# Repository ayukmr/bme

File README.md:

# bme

Surge concussion detector PCB for BME.

## Schematic

## PCB

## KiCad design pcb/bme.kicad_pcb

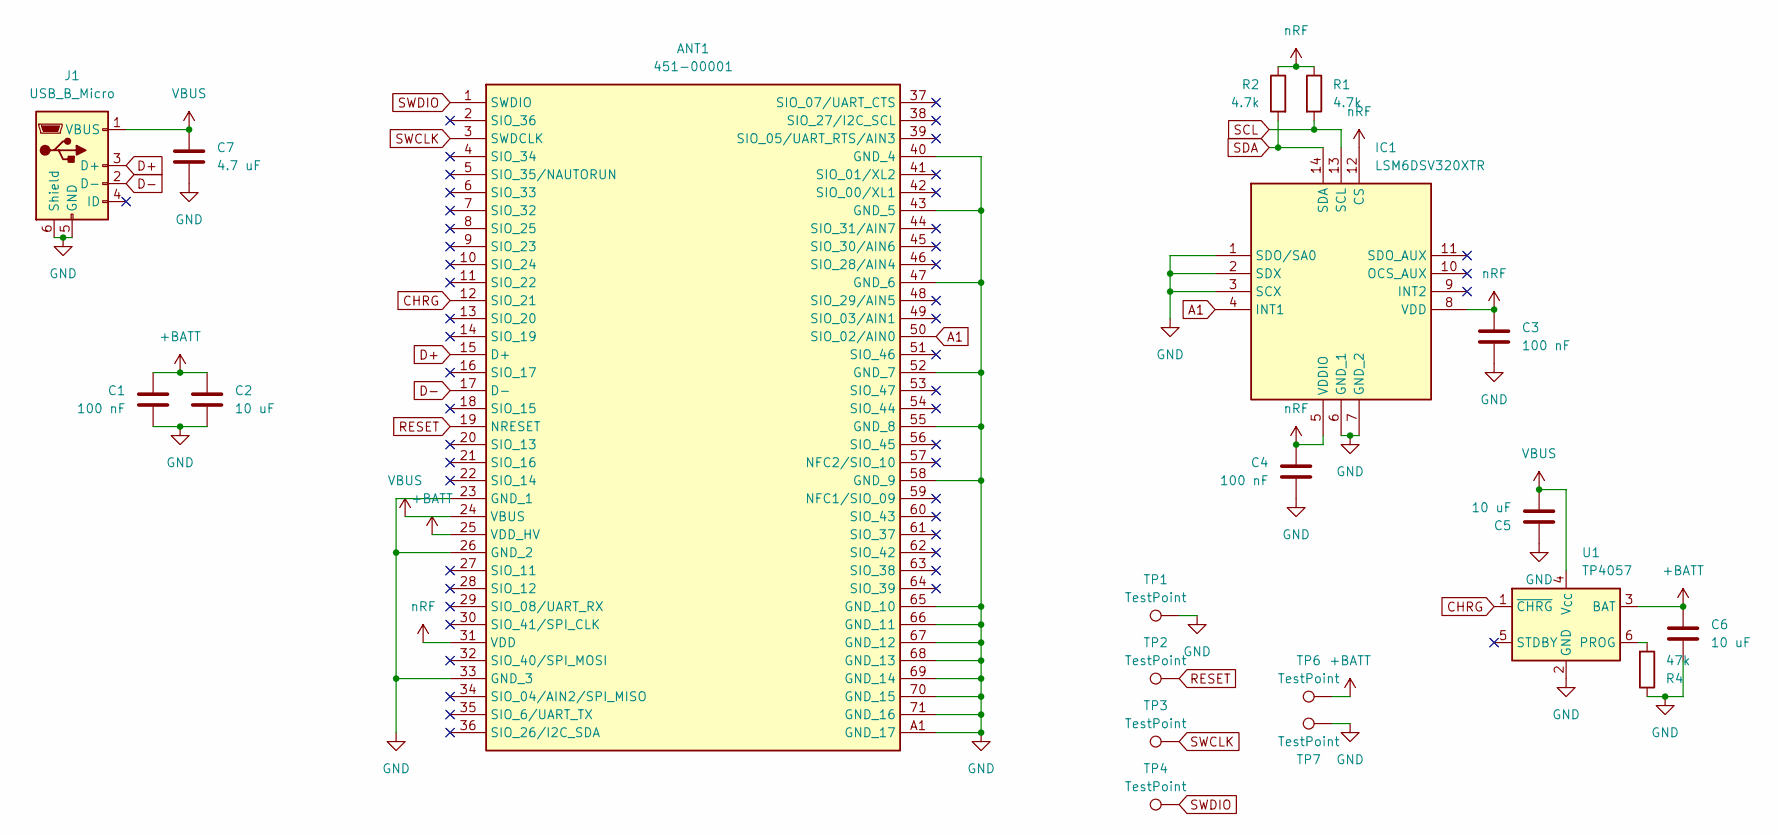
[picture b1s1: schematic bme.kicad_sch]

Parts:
ANT1: 451-00001; 45100001; Manufacturer_Part_Number 451-00001; Mouser Part Number 814-451-00001
C1, C3, C4: 100 nF; C_0603_1608Metric
C2, C5, C6: 10 uF; C_0603_1608Metric
C7: 4.7 uF; C_0603_1608Metric
IC1: LSM6DSV320XTR; LGA-14_3x2.5mm_P0.5mm_LayoutBorder3x4y; Manufacturer_Part_Number LSM6DSV320XTR; Mouser Part Number 511-LSM6DSV320XTR
J1: USB_B_Micro; MICRO-USB-SMD_47346-0001
R1, R2: 4.7k; R_0603_1608Metric
R4: 47k; R_0603_1608Metric
TP1, TP2, TP3, TP4, TP6, TP7: TestPoint; Pad_SMD_1.5x1.5
U1: TP4057; TSOT-23-6

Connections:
+BATT: ANT1.25 (VDD_HV), C1.2, C2.1, C6.2, TP6.1 (1_1), U1.3 (BAT)
A1: ANT1.50 (SIO_02/AIN0), IC1.4 (INT1)
CHRG: ANT1.12 (SIO_21), U1.1 (~CHRG)
D+: ANT1.15 (D+), J1.3 (D+)
D-: ANT1.17 (D-), J1.2 (D-)
GND: ANT1.23 (GND_1), ANT1.26 (GND_2), ANT1.33 (GND_3), ANT1.40 (GND_4), ANT1.43 (GND_5), ANT1.47 (GND_6), ANT1.52 (GND_7), ANT1.55 (GND_8), ANT1.58 (GND_9), ANT1.65 (GND_10), ANT1.66 (GND_11), ANT1.67 (GND_12), ANT1.68 (GND_13), ANT1.69 (GND_14), ANT1.70 (GND_15), ANT1.71 (GND_16), ANT1.A1 (GND_17), C1.1, C2.2, C3.2, C4.2, C5.1, C6.1, C7.1, IC1.1 (SDO/SA0), IC1.2 (SDX), IC1.3 (SCX), IC1.6 (GND_1), IC1.7 (GND_2), J1.5 (GND), J1.6 (Shield), R4.1, TP1.1 (1_1), TP7.1 (1_1), U1.2 (GND)
unnamed: R4.2, U1.6 (PROG)
RESET: ANT1.19 (NRESET), TP2.1 (1_1)
SCL: IC1.13 (SCL), R1.2
SDA: IC1.14 (SDA), R2.2
SWCLK: ANT1.3 (SWDCLK), TP3.1 (1_1)
SWDIO: ANT1.1 (SWDIO), TP4.1 (1_1)
VBUS: ANT1.24 (VBUS), C5.2, C7.2, J1.1 (VBUS), U1.4 (V_{CC})
nRF: ANT1.31 (VDD), C3.1, C4.1, IC1.5 (VDDIO), IC1.8 (VDD), IC1.12 (CS), R1.1, R2.1

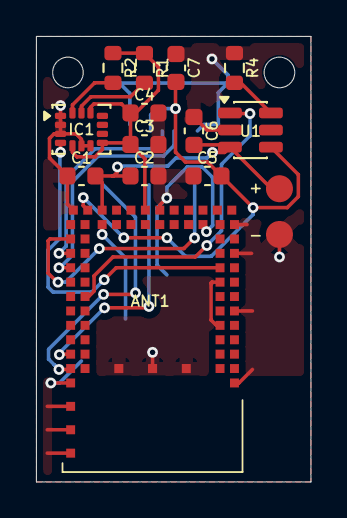
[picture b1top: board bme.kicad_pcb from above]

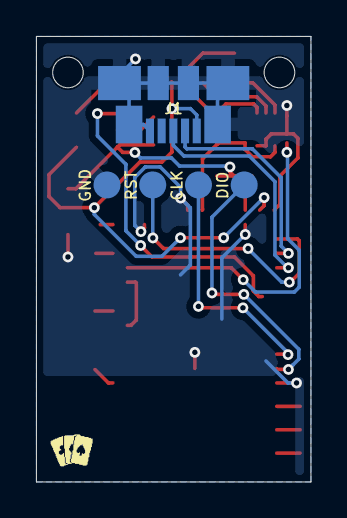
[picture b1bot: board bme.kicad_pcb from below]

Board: 2 copper layers, 15.2 x 24.8 mm, 20 parts (5 on the bottom side), 14 nets.
